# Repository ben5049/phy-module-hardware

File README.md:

# PHY Module Hardware

## 10BASE-T1S v1

[Errata](/docs/errata.md#1-10base-t1s-phy-module-v1)

## 1000BASE-T1 v1

[Errata](/docs/errata.md#2-1000base-t1-phy-module-v1)

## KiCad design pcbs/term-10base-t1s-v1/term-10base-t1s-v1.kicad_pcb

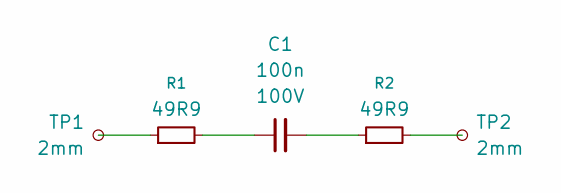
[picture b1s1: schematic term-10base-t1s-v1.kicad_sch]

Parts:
C1: 100n; C_0402_1005Metric; Voltage 100V
R1, R2: 49R9; R_0402_1005Metric
TP1, TP2: 2mm; TestPoint_Pad_D2.0mm

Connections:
unnamed: C1.1, R1.2
unnamed: C1.2, R2.1
unnamed: R1.1, TP1.1 (1_1)
unnamed: R2.2, TP2.1 (1_1)

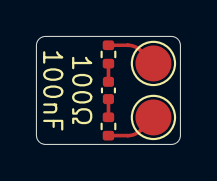
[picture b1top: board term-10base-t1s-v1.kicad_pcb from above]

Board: 2 copper layers, 8.0 x 6.0 mm, 5 parts (0 on the bottom side), 4 nets.

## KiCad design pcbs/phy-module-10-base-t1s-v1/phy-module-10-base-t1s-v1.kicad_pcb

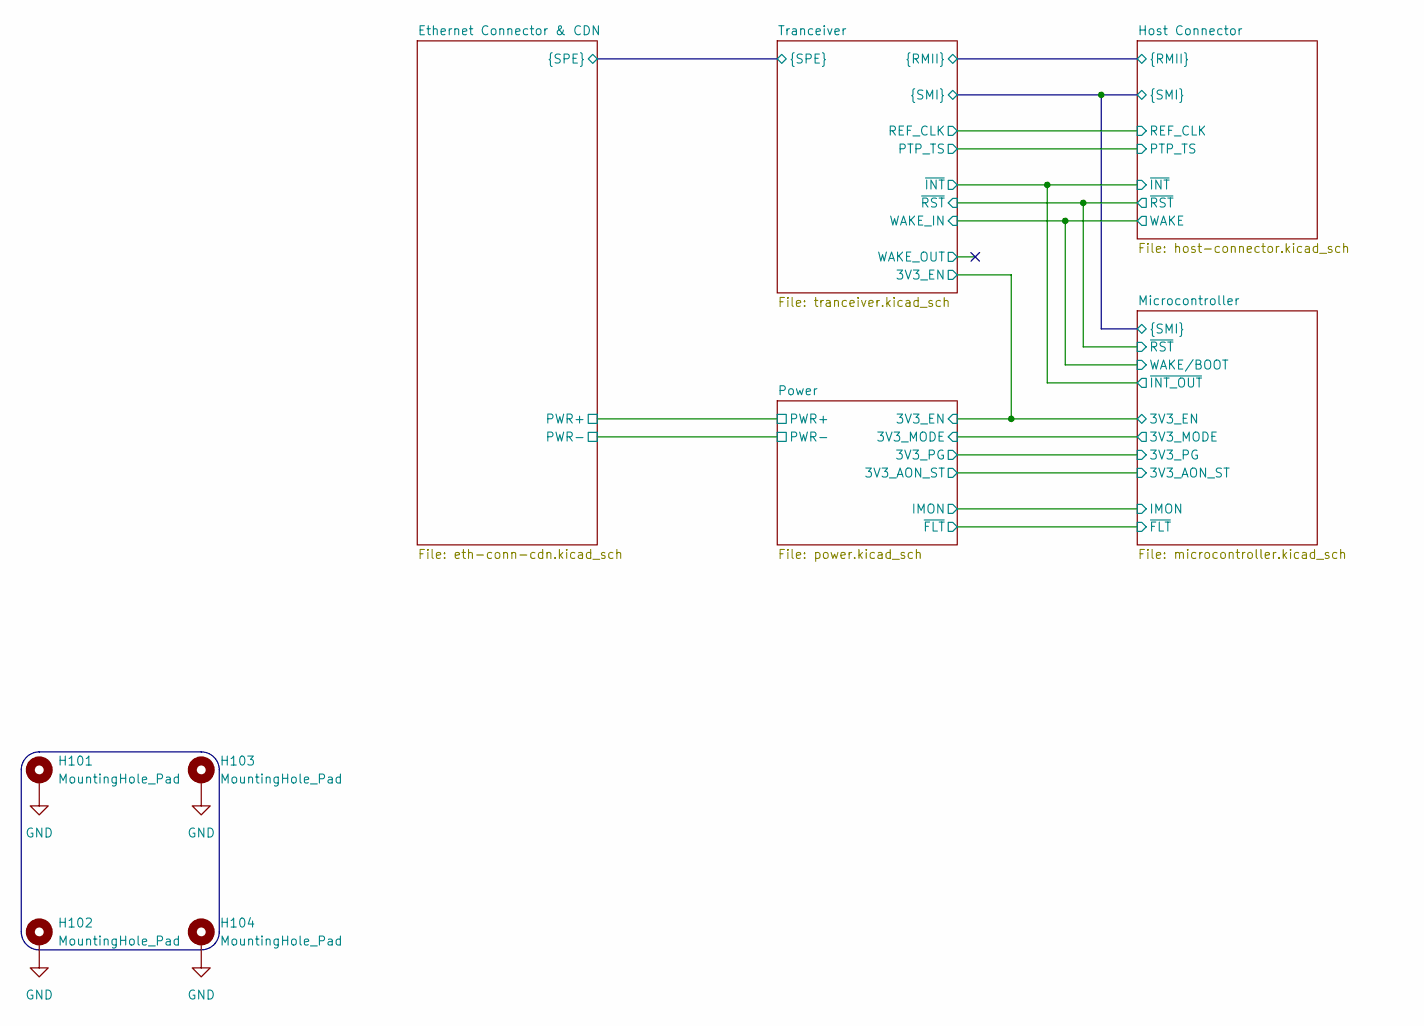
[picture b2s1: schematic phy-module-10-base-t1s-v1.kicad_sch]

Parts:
H101, H102, H103, H104: MountingHole_Pad; MountingHole_2.7mm_M2.5_Pad

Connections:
GND: H101.1 (1_1), H102.1 (1_1), H103.1 (1_1), H104.1 (1_1); also elsewhere on the board

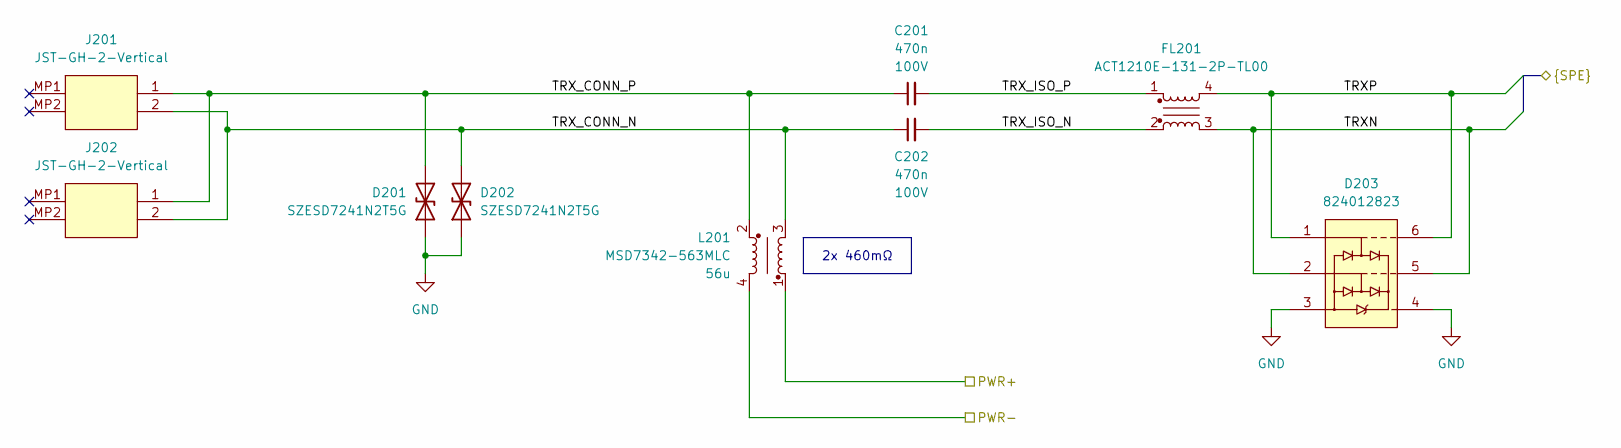
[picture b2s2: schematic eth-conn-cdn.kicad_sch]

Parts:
C201, C202: 470n; C_0805; Voltage 100V
D201, D202: SZESD7241N2T5G; SZESD7462N2T5G; Mouser Part Number 863-SZESD7241N2T5G
D203: 824012823; Mouser Part Number 710-824012823
FL201: ACT1210E-131-2P-TL00; ACT1210E; Mouser Part Number 810-ACT1210E1312PTL0
J201, J202: JST-GH-2-Vertical; JST_GH_BM02B-GHS-TBT_1x02-1MP_P1.25mm_Vertical
L201: MSD7342-563MLC; MSD7342

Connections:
/Ethernet Connector & CDN/PWR+: L201.1; also elsewhere on the board
/Ethernet Connector & CDN/PWR-: L201.4 (2); also elsewhere on the board
/Ethernet Connector & CDN/TRXN: D203.2, D203.5, FL201.3; also elsewhere on the board
/Ethernet Connector & CDN/TRXP: D203.1, D203.6, FL201.4; also elsewhere on the board
/Ethernet Connector & CDN/TRX_CONN_N: C202.1, D202.2 (A2), J201.2, J202.2, L201.3
/Ethernet Connector & CDN/TRX_CONN_P: C201.1, D201.2 (A2), J201.1, J202.1, L201.2 (4)
/Ethernet Connector & CDN/TRX_ISO_N: C202.2, FL201.2
/Ethernet Connector & CDN/TRX_ISO_P: C201.2, FL201.1
GND: D201.1 (A1), D202.1 (A1), D203.3, D203.4; also elsewhere on the board

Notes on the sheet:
2x 460mΩ

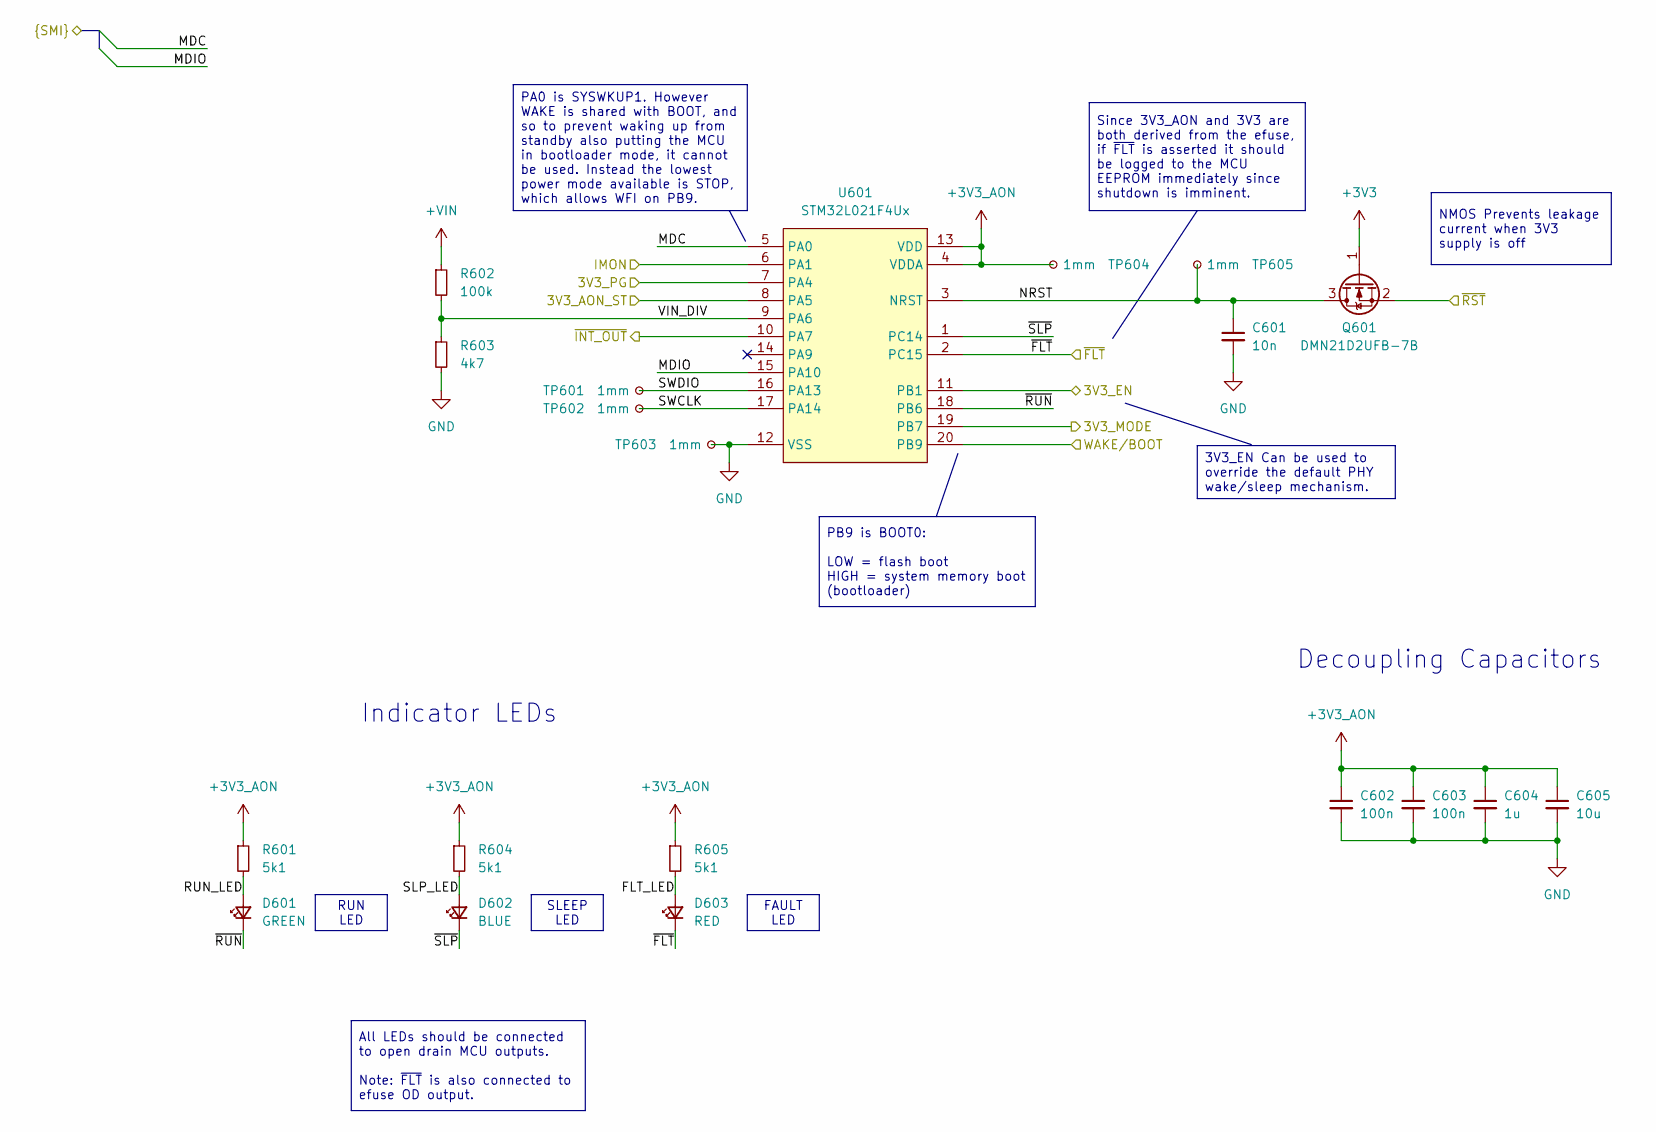
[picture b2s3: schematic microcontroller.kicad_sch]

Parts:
C601: 10n; C_0402
C602, C603: 100n; C_0402
C604: 1u; C_0402
C605: 10u; C_0402
D601: GREEN; LED_0402
D602: BLUE; LED_0402
D603: RED; LED_0402
Q601: DMN21D2UFB-7B; DMN21D2UFB7B; Mouser Part Number 621-DMN21D2UFB-7B
R601, R604, R605: 5k1; R_0402
R602: 100k; R_0402
R603: 4k7; R_0402
TP601, TP602, TP603, TP604, TP605: 1mm; TestPoint_Pad_D1.0mm
U601: STM32L021F4Ux; ST_UFQFPN-20_3x3mm_P0.5mm

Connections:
+3V3: Q601.1 (G); also elsewhere on the board
+3V3_AON: C602.1, C603.1, C604.1, C605.1, R601.1, R604.1, R605.1, TP604.1 (1_1), U601.4 (VDDA), U601.13 (VDD); also elsewhere on the board
+VIN: R602.1; also elsewhere on the board
/Host Connector/MDC: U601.5 (PA0); also elsewhere on the board
/Host Connector/MDIO: U601.15 (PA10); also elsewhere on the board
/Host Connector/WAKE: U601.20 (PB9); also elsewhere on the board
/Host Connector/~INT: U601.10 (PA7); also elsewhere on the board
/Host Connector/~RST: Q601.2 (S); also elsewhere on the board
/Microcontroller/3V3_AON_ST: U601.8 (PA5); also elsewhere on the board
/Microcontroller/3V3_EN: U601.11 (PB1); also elsewhere on the board
/Microcontroller/3V3_MODE: U601.19 (PB7); also elsewhere on the board
/Microcontroller/FLT_LED: D603.2 (A), R605.2
/Microcontroller/IMON: U601.6 (PA1); also elsewhere on the board
/Microcontroller/NRST: C601.1, Q601.3 (D), TP605.1 (1_1), U601.3 (NRST)
/Microcontroller/RUN_LED: D601.2 (A), R601.2
/Microcontroller/SLP_LED: D602.2 (A), R604.2
/Microcontroller/SWCLK: TP602.1 (1_1), U601.17 (PA14)
/Microcontroller/SWDIO: TP601.1 (1_1), U601.16 (PA13)
/Microcontroller/VIN_DIV: R602.2, R603.1, U601.9 (PA6)
/Microcontroller/~FLT: D603.1 (K), U601.2 (PC15); also elsewhere on the board
/Microcontroller/~RUN: D601.1 (K), U601.18 (PB6)
/Microcontroller/~SLP: D602.1 (K), U601.1 (PC14)
/Power/3V3_PG: U601.7 (PA4); also elsewhere on the board
GND: C601.2, C602.2, C603.2, C604.2, C605.2, R603.2, TP603.1 (1_1), U601.12 (VSS); also elsewhere on the board

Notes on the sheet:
Decoupling Capacitors
Indicator LEDs
RUN LED
PA0 is SYSWKUP1. However WAKE is shared with BOOT, and so to prevent waking up from standby also putting the MCU in bootloader mode, it cannot be used. Instead the lowest power mode available is STOP, which allows WFI on PB9.
PB9 is BOOT0: LOW = flash boot HIGH = system memory boot (bootloader)
FAULT LED
Since 3V3_AON and 3V3 are both derived from the efuse, if ~{FLT} is asserted it should be logged to the MCU EEPROM immediately since shutdown is imminent.
SLEEP LED
All LEDs should be connected to open drain MCU outputs. Note: ~{FLT} is also connected to efuse OD output.
3V3_EN Can be used to override the default PHY wake/sleep mechanism.
NMOS Prevents leakage current when 3V3 supply is off

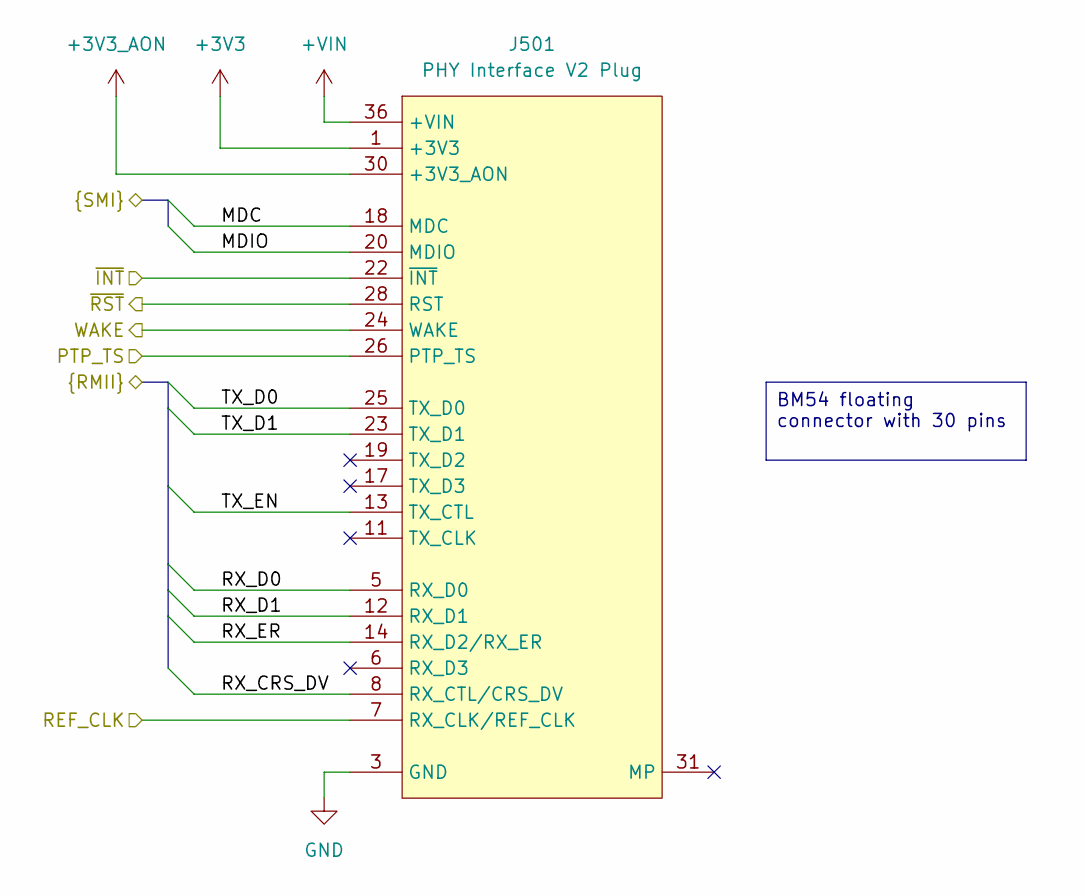
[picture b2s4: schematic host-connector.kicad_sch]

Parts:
J501: PHY Interface V2 Plug; BM54F3030DP04V51-PWR

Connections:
+3V3: J501.1 (+3V3), J501.2 (+3V3), J501.29 (+3V3); also elsewhere on the board
+3V3_AON: J501.30 (+3V3_AON); also elsewhere on the board
+VIN: J501.36 (+VIN); also elsewhere on the board
/Host Connector/MDC: J501.18 (MDC); also elsewhere on the board
/Host Connector/MDIO: J501.20 (MDIO); also elsewhere on the board
/Host Connector/PTP_TS: J501.26 (PTP_TS); also elsewhere on the board
/Host Connector/REF_CLK: J501.7 (RX_CLK/REF_CLK); also elsewhere on the board
/Host Connector/RX_CRS_DV: J501.8 (RX_CTL/CRS_DV); also elsewhere on the board
/Host Connector/RX_D0: J501.5 (RX_D0); also elsewhere on the board
/Host Connector/RX_D1: J501.12 (RX_D1); also elsewhere on the board
/Host Connector/RX_ER: J501.14 (RX_D2/RX_ER); also elsewhere on the board
/Host Connector/TX_D0: J501.25 (TX_D0); also elsewhere on the board
/Host Connector/TX_D1: J501.23 (TX_D1); also elsewhere on the board
/Host Connector/TX_EN: J501.13 (TX_CTL); also elsewhere on the board
/Host Connector/WAKE: J501.24 (WAKE); also elsewhere on the board
/Host Connector/~INT: J501.22 (~INT); also elsewhere on the board
/Host Connector/~RST: J501.28 (RST); also elsewhere on the board
GND: J501.3 (GND), J501.4 (GND), J501.9 (GND), J501.10 (GND), J501.15 (GND), J501.16 (GND), J501.21 (GND), J501.27 (GND), J501.35 (GND); also elsewhere on the board

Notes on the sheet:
BM54 floating connector with 30 pins

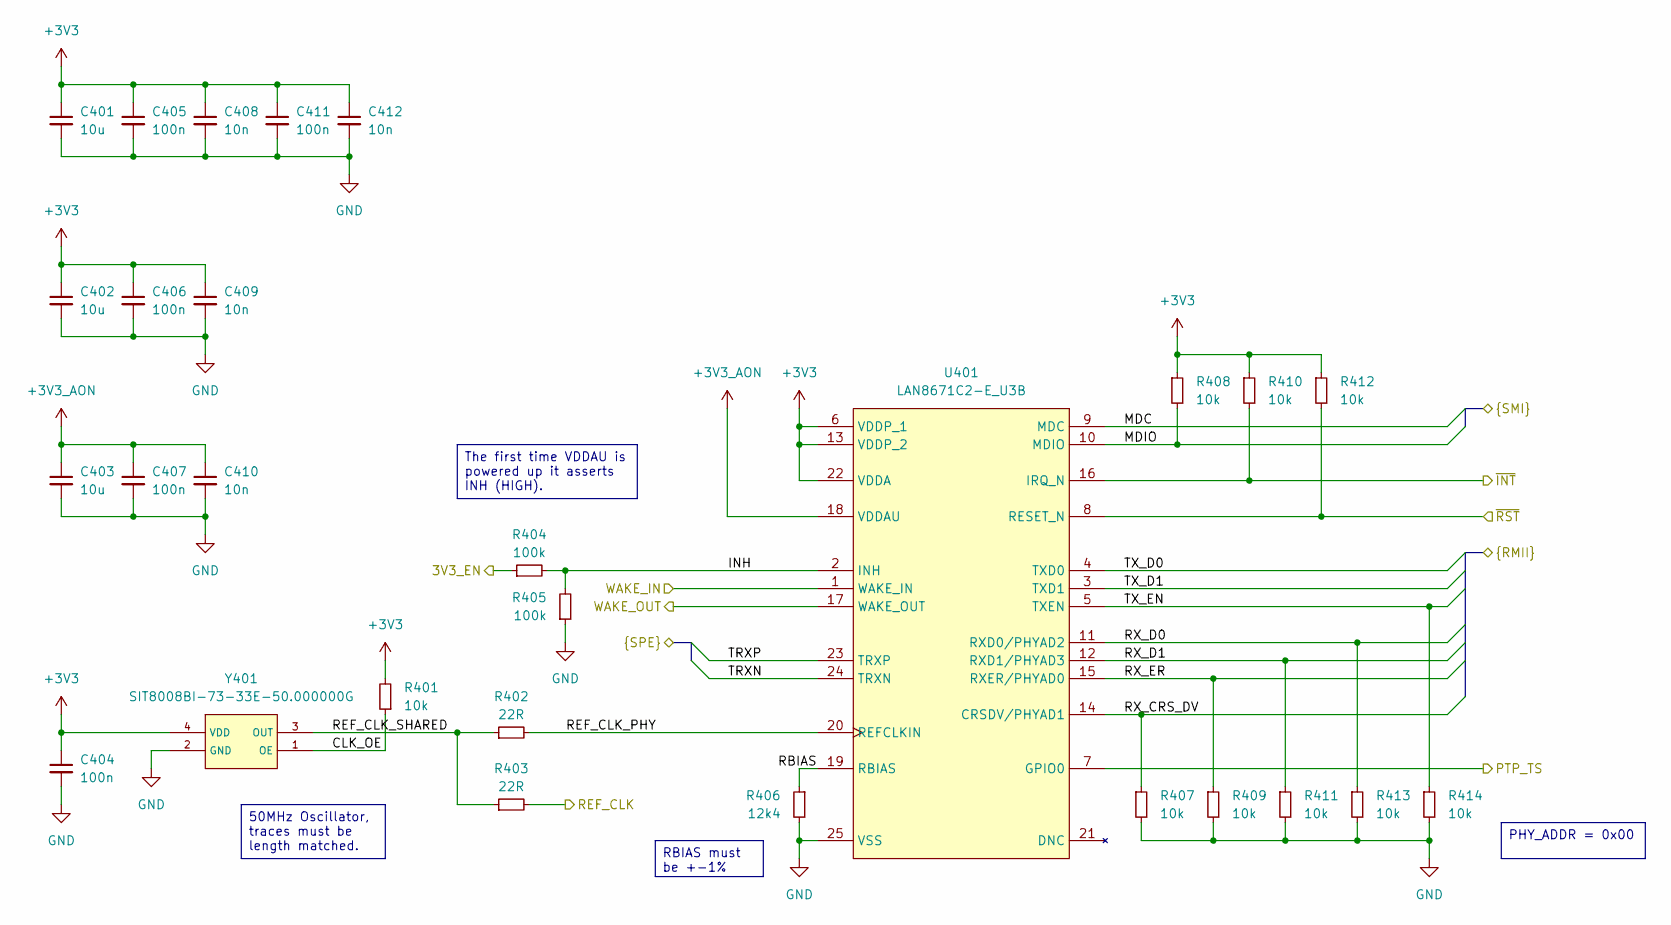
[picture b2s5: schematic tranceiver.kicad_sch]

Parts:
C401, C402, C403: 10u; C_0402
C404, C405, C406, C407, C411: 100n; C_0402
C408, C409, C410, C412: 10n; C_0402
R401, R407, R408, R409, R410, R411, R412, R413, R414: 10k; R_0402
R402, R403: 22R; R_0402
R404, R405: 100k; R_0402
R406: 12k4; R_0402
U401: LAN8671C2-E_U3B; QFN50P400X400X100-25N-D; Mouser Part Number 579-LAN8671C2-E/U3B
Y401: SIT8008BI-73-33E-50.000000G; SiTime-SiT8008-7-0-0-MFG; mouser part number 788-8008BI7333E500G; digikey description MEMS OSC XO 50.0000MHZ H/LV-CMOS

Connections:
+3V3: C401.1, C402.1, C404.1, C405.1, C406.1, C408.1, C409.1, C411.1, C412.1, R401.2, R408.1, R410.1, R412.1, U401.6 (VDDP_1), U401.13 (VDDP_2), U401.22 (VDDA), Y401.4 (VDD); also elsewhere on the board
+3V3_AON: C403.1, C407.1, C410.1, U401.18 (VDDAU); also elsewhere on the board
/Ethernet Connector & CDN/TRXN: U401.24 (TRXN); also elsewhere on the board
/Ethernet Connector & CDN/TRXP: U401.23 (TRXP); also elsewhere on the board
/Host Connector/MDC: U401.9 (MDC); also elsewhere on the board
/Host Connector/MDIO: R408.2, U401.10 (MDIO); also elsewhere on the board
/Host Connector/PTP_TS: U401.7 (GPIO0); also elsewhere on the board
/Host Connector/REF_CLK: R403.2; also elsewhere on the board
/Host Connector/RX_CRS_DV: R407.1, U401.14 (CRSDV/PHYAD1); also elsewhere on the board
/Host Connector/RX_D0: R413.1, U401.11 (RXD0/PHYAD2); also elsewhere on the board
/Host Connector/RX_D1: R411.1, U401.12 (RXD1/PHYAD3); also elsewhere on the board
/Host Connector/RX_ER: R409.1, U401.15 (RXER/PHYAD0); also elsewhere on the board
/Host Connector/TX_D0: U401.4 (TXD0); also elsewhere on the board
/Host Connector/TX_D1: U401.3 (TXD1); also elsewhere on the board
/Host Connector/TX_EN: R414.1, U401.5 (TXEN); also elsewhere on the board
/Host Connector/WAKE: U401.1 (WAKE_IN); also elsewhere on the board
/Host Connector/~INT: R410.2, U401.16 (IRQ_N); also elsewhere on the board
/Host Connector/~RST: R412.2, U401.8 (RESET_N); also elsewhere on the board
/Microcontroller/3V3_EN: R404.1; also elsewhere on the board
/Tranceiver/CLK_OE: R401.1, Y401.1 (OE)
/Tranceiver/INH: R404.2, R405.2, U401.2 (INH)
/Tranceiver/RBIAS: R406.1, U401.19 (RBIAS)
/Tranceiver/REF_CLK_PHY: R402.2, U401.20 (REFCLKIN)
/Tranceiver/REF_CLK_SHARED: R402.1, R403.1, Y401.3 (OUT)
/Tranceiver/WAKE_OUT: U401.17 (WAKE_OUT)
GND: C401.2, C402.2, C403.2, C404.2, C405.2, C406.2, C407.2, C408.2, C409.2, C410.2, C411.2, C412.2, R405.1, R406.2, R407.2, R409.2, R411.2, R413.2, R414.2, U401.25 (VSS), Y401.2 (GND); also elsewhere on the board

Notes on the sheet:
50MHz Oscillator, traces must be length matched.
PHY_ADDR = 0x00
RBIAS must be +-1%
The first time VDDAU is powered up it asserts INH (HIGH).

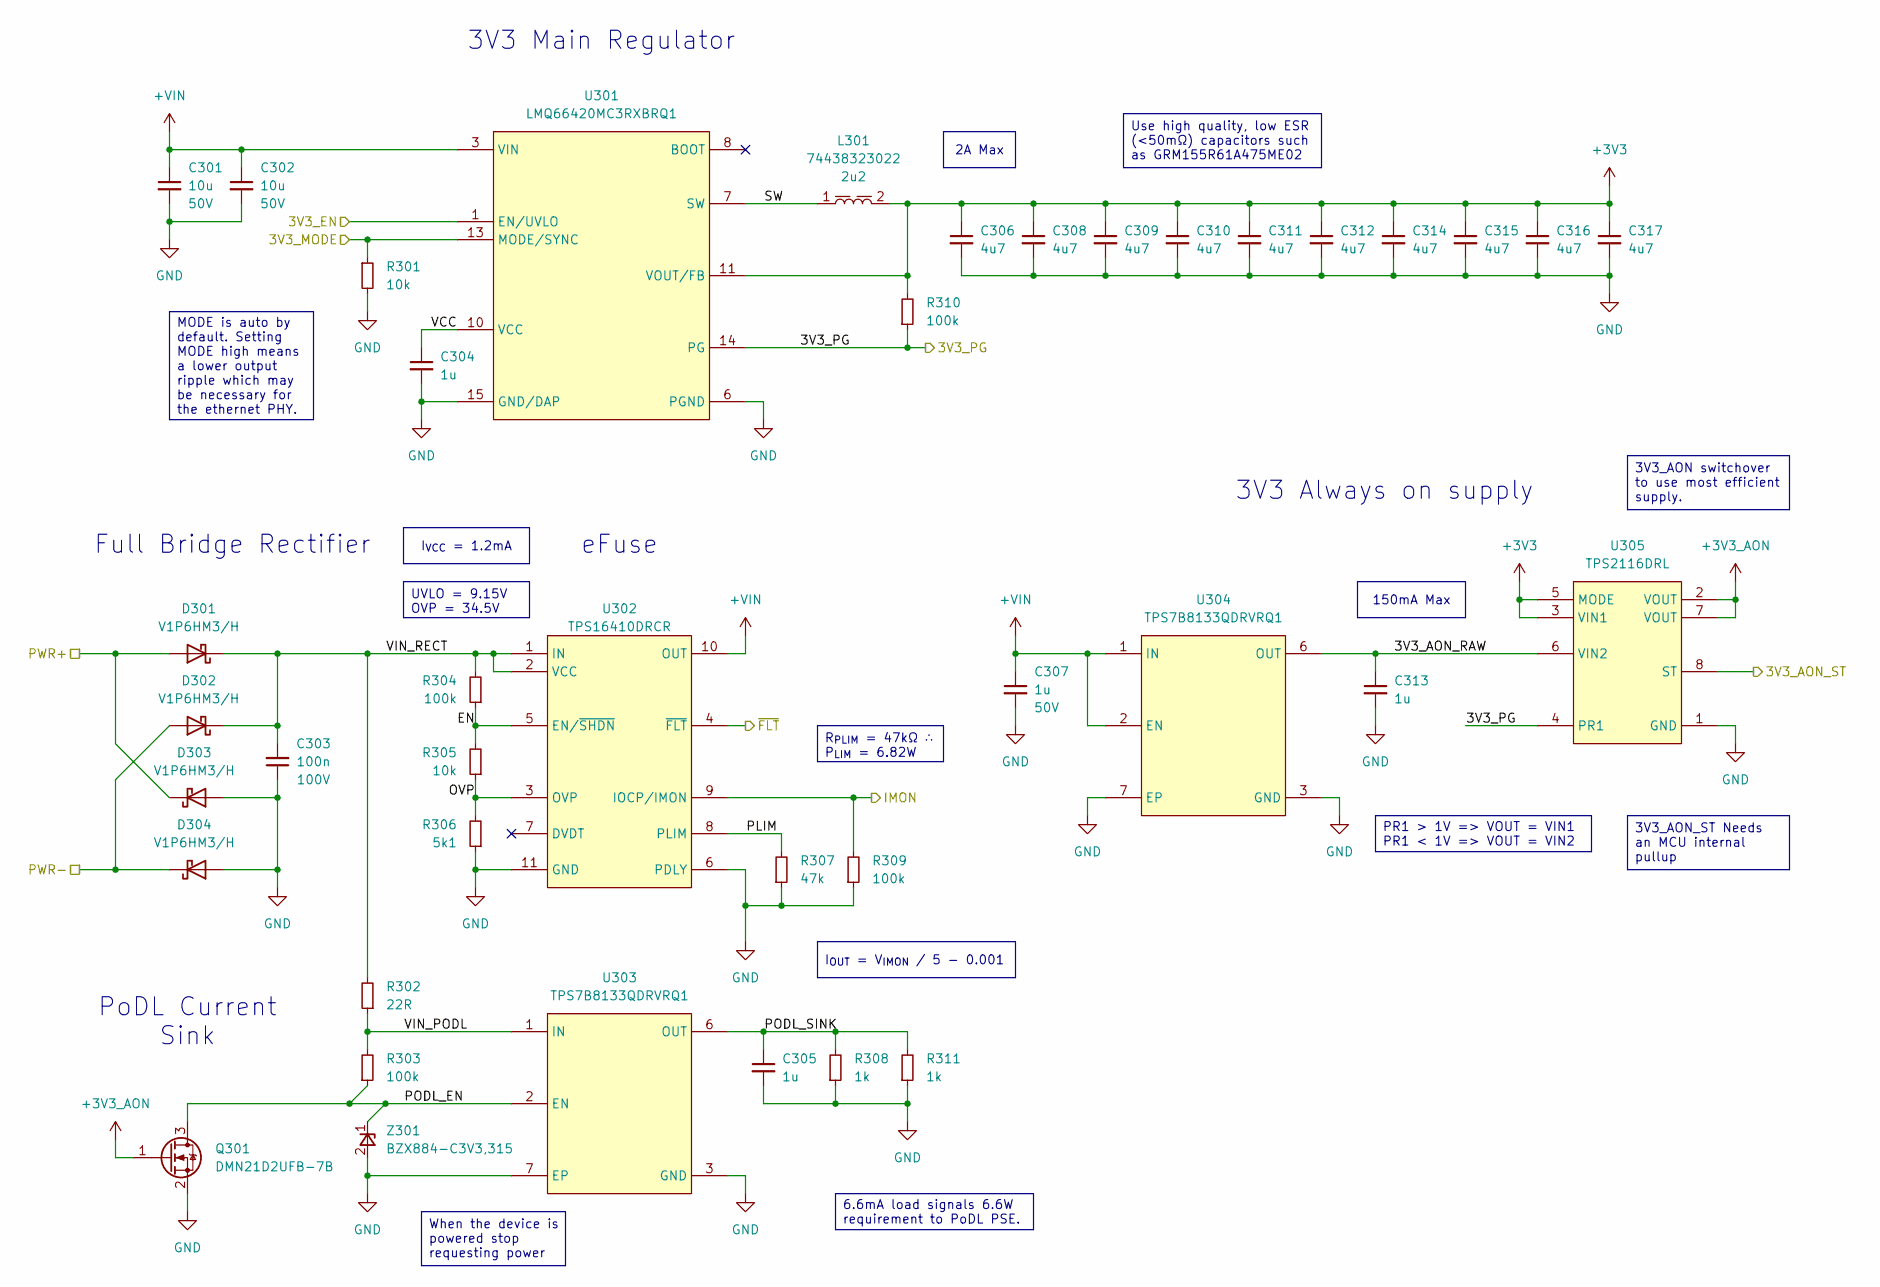
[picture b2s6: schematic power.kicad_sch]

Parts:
C301, C302: 10u; C_0805; Voltage 50V
C303: 100n; C_0402; Voltage 100V
C304, C305, C313: 1u; C_0402
C306, C308, C309, C310, C311, C312, C314, C315, C316, C317: 4u7; C_0402
C307: 1u; C_0402; Voltage 50V
D301, D302, D303, D304: V1P6HM3/H; V1P6HM3_H
L301: 74438323022; L_Wurth_WE-MAPI-2510; Part Number 74438323022
Q301: DMN21D2UFB-7B; DMN21D2UFB7B; Mouser Part Number 621-DMN21D2UFB-7B
R301, R305: 10k; R_0402
R302: 22R; R_0402
R303, R304, R309, R310: 100k; R_0402
R306: 5k1; R_0402
R307: 47k; R_0402
R308, R311: 1k; R_0402
U301: LMQ66420MC3RXBRQ1; LMQ664x0
U302: TPS16410DRCR; Mouser Part Number 595-TPS16410DRCR
U303, U304: TPS7B8133QDRVRQ1; SON65P200X200X80-7N; Mouser Part Number 595-TPS7B8133QDRVRQ1
U305: TPS2116DRL; SOTFL50P160X60-8N
Z301: BZX884-C3V3,315; BZX884; Mouser Part Number 771-BZX884-C3V9315

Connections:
+3V3: C306.1, C308.1, C309.1, C310.1, C311.1, C312.1, C314.1, C315.1, C316.1, C317.1, L301.2, R310.2, U301.11 (VOUT/FB), U305.3 (VIN1), U305.5 (MODE); also elsewhere on the board
+3V3_AON: Q301.1 (G), U305.2 (VOUT), U305.7 (VOUT); also elsewhere on the board
+VIN: C301.1, C302.1, C307.1, U301.3 (VIN), U302.10 (OUT), U304.1 (IN), U304.2 (EN); also elsewhere on the board
/Ethernet Connector & CDN/PWR+: D301.2 (A), D303.1 (K); also elsewhere on the board
/Ethernet Connector & CDN/PWR-: D302.2 (A), D304.1 (K); also elsewhere on the board
/Microcontroller/3V3_AON_ST: U305.8 (ST); also elsewhere on the board
/Microcontroller/3V3_EN: U301.1 (EN/UVLO); also elsewhere on the board
/Microcontroller/3V3_MODE: R301.1, U301.13 (MODE/SYNC); also elsewhere on the board
/Microcontroller/IMON: R309.2, U302.9 (IOCP/IMON); also elsewhere on the board
/Microcontroller/~FLT: U302.4 (~FLT); also elsewhere on the board
/Power/3V3_AON_RAW: C313.1, U304.6 (OUT), U305.6 (VIN2)
/Power/3V3_PG: R310.1, U301.14 (PG), U305.4 (PR1); also elsewhere on the board
/Power/EN: R304.1, R305.2, U302.5 (EN/~SHDN)
/Power/OVP: R305.1, R306.2, U302.3 (OVP)
/Power/PLIM: R307.2, U302.8 (PLIM)
/Power/PODL_EN: Q301.3 (D), R303.1, U303.2 (EN), Z301.1 (K)
/Power/PODL_SINK: C305.1, R308.2, R311.2, U303.6 (OUT)
/Power/SW: L301.1, U301.7 (SW)
/Power/VCC: C304.1, U301.10 (VCC)
/Power/VIN_PODL: R302.1, R303.2, U303.1 (IN)
/Power/VIN_RECT: C303.2, D301.1 (K), D302.1 (K), R302.2, R304.2, U302.1 (IN), U302.2 (VCC)
GND: C301.2, C302.2, C303.1, C304.2, C305.2, C306.2, C307.2, C308.2, C309.2, C310.2, C311.2, C312.2, C313.2, C314.2, C315.2, C316.2, C317.2, D303.2 (A), D304.2 (A), Q301.2 (S), R301.2, R306.1, R307.1, R308.1, R309.1, R311.1, U301.6 (PGND), U301.15 (GND/DAP), U302.6 (PDLY), U302.11 (GND), U302.12 (GND), U302.13 (GND), U302.14 (GND), U302.15 (GND), U303.3 (GND), U303.4 (GND), U303.7 (EP), U304.3 (GND), U304.4 (GND), U304.7 (EP), U305.1 (GND), Z301.2 (A); also elsewhere on the board

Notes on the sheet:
Full Bridge Rectifier
PoDL Current Sink
3V3 Main Regulator
3V3 Always on supply
eFuse
R_{PLIM} = 47kΩ ∴ P_{LIM} = 6.82W
UVLO = 9.15V OVP = 34.5V
MODE is auto by default. Setting MODE high means a lower output ripple which may be necessary for the ethernet PHY.
When the device is powered stop requesting power
PR1 > 1V => VOUT = VIN1 PR1 < 1V => VOUT = VIN2
3V3_AON switchover to use most efficient supply.
2A Max
Use high quality, low ESR (<50mΩ) capacitors such as GRM155R61A475ME02
150mA Max
3V3_AON_ST Needs an MCU internal pullup
6.6mA load signals 6.6W requirement to PoDL PSE.
I_{VCC} = 1.2mA
I_{OUT} = V_{IMON} / 5 - 0.001

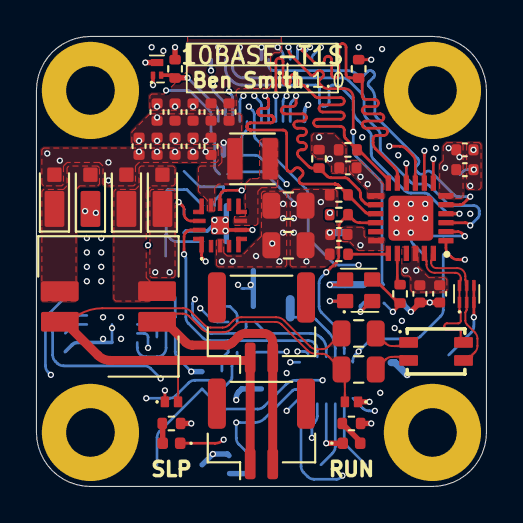
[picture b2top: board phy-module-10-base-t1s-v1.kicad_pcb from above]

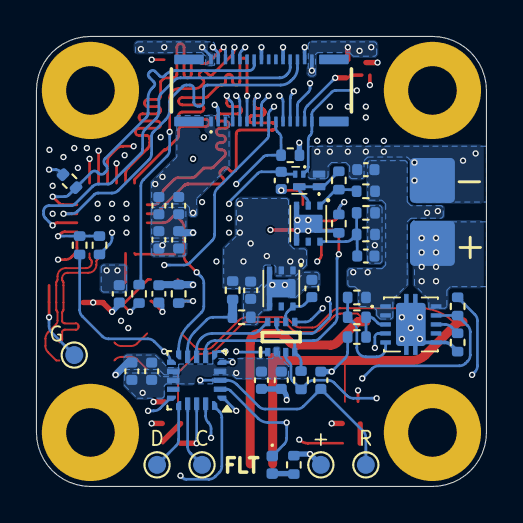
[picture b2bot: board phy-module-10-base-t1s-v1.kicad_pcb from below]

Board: 6 copper layers, 25.0 x 25.0 mm, 102 parts (50 on the bottom side), 56 nets.

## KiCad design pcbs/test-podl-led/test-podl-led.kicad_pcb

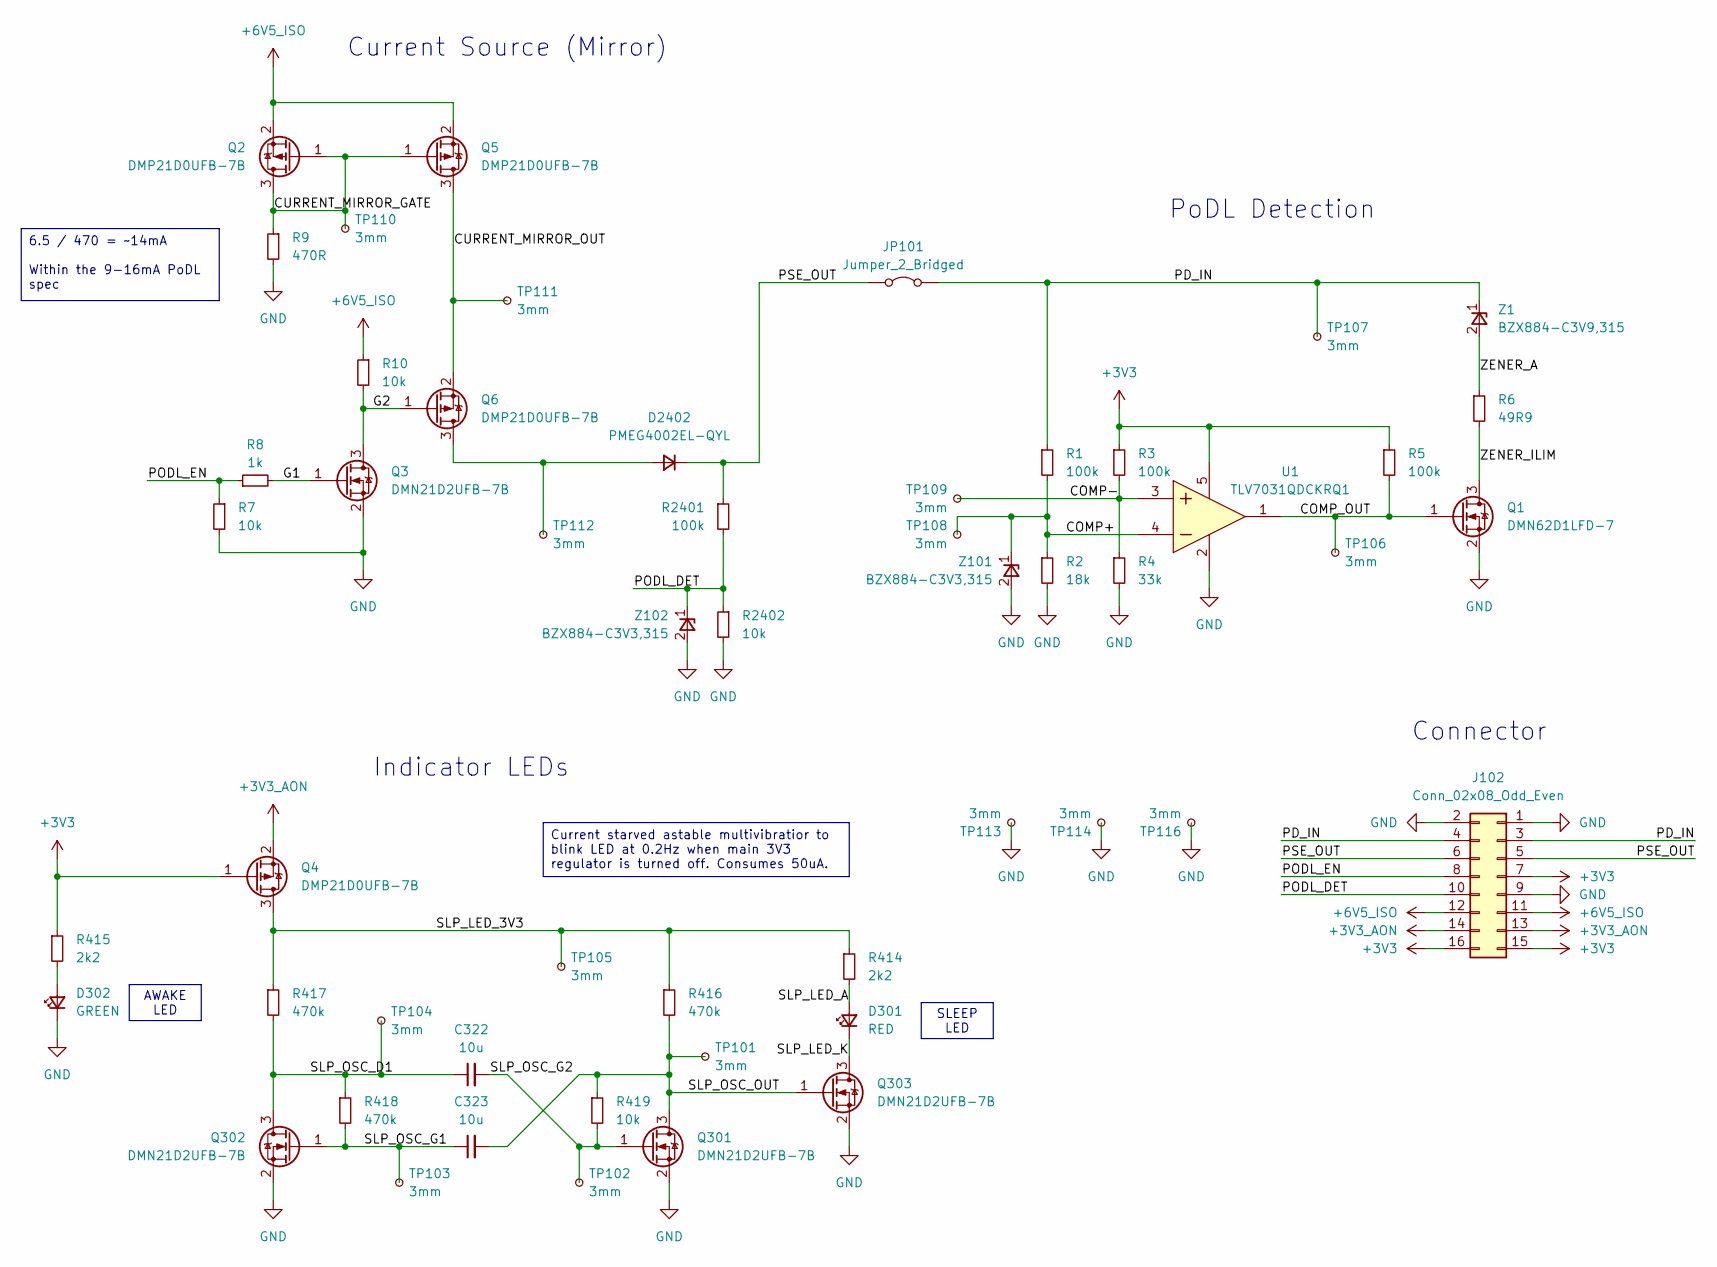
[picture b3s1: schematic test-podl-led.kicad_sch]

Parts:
C322, C323: 10u; C_0402_1005Metric
D301: RED; LED_0402_1005Metric
D302: GREEN; LED_0402_1005Metric
D2402: PMEG4002EL-QYL
J102: Conn_02x08_Odd_Even; PinHeader_2x08_P2.54mm_Vertical
JP101: Jumper_2_Bridged; PinHeader_1x02_P2.54mm_Vertical
Q1: DMN62D1LFD-7; DMN62D1LFD; Mouser Part Number 621-DMN62D1LFD-7
Q2, Q4, Q5, Q6: DMP21D0UFB-7B; DMP21D0UFB7B; Mouser Part Number 621-DMP21D0UFB-7B
Q3, Q301, Q302, Q303: DMN21D2UFB-7B; DMN21D2UFB7B; Mouser Part Number 621-DMN21D2UFB-7B
R1, R3, R5, R2401: 100k; R_0402_1005Metric
R2: 18k; R_0402_1005Metric
R4: 33k; R_0402_1005Metric
R6: 49R9; R_0402_1005Metric
R7, R10, R419, R2402: 10k; R_0402_1005Metric
R8: 1k; R_0402_1005Metric
R9: 470R; R_0402_1005Metric
R414, R415: 2k2; R_0402_1005Metric
R416, R417, R418: 470k; R_0402_1005Metric
TP101, TP102, TP103, TP104, TP105, TP106, TP107, TP108, TP109, TP110, TP111, TP112, TP113, TP114, TP116: 3mm; TestPoint_Pad_D3.0mm
U1: TLV7031QDCKRQ1; SOT65P210X110-5N; Mouser Part Number 595-TLV7031QDCKRQ1
Z1: BZX884-C3V9,315; BZX884; Mouser Part Number 771-BZX884-C3V9315
Z101, Z102: BZX884-C3V3,315; BZX884; Mouser Part Number 771-BZX884-C3V9315

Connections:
+3V3: J102.7, J102.15, J102.16, Q4.1 (G), R3.1, R5.1, R415.1, U1.5 (VCC)
+3V3_AON: J102.13, J102.14, Q4.2 (S)
+6V5_ISO: J102.11, J102.12, Q2.2 (S), Q5.2 (S), R10.1
/COMP+: R1.2, R2.1, TP108.1, U1.4 (IN-), Z101.1 (K)
/COMP-: R3.2, R4.1, TP109.1, U1.3 (IN+)
/COMP_OUT: Q1.1 (G), R5.2, TP106.1, U1.1 (OUT)
/CURRENT_MIRROR_GATE: Q2.1 (G), Q2.3 (D), Q5.1 (G), R9.1, TP110.1
/CURRENT_MIRROR_OUT: Q5.3 (D), Q6.2 (S), TP111.1
/G1: Q3.1 (G), R8.2
/G2: Q3.3 (D), Q6.1 (G), R10.2
/PD_IN: J102.3, J102.4, JP101.2 (B), R1.1, TP107.1, Z1.1 (K)
/PODL_DET: J102.10, R2401.2, R2402.1, Z102.1 (K)
/PODL_EN: J102.8, R7.1, R8.1
/PSE_OUT: D2402.1 (K), J102.5, J102.6, JP101.1 (A), R2401.1
/SLP_LED_3V3: Q4.3 (D), R414.1, R416.1, R417.1, TP105.1
/SLP_LED_A: D301.2 (A), R414.2
/SLP_LED_K: D301.1 (K), Q303.3 (D)
/SLP_OSC_D1: C322.1, Q302.3 (D), R417.2, R418.1, TP104.1
/SLP_OSC_G1: C323.1, Q302.1 (G), R418.2, TP103.1
/SLP_OSC_G2: C322.2, Q301.1 (G), R419.2, TP102.1
/SLP_OSC_OUT: C323.2, Q301.3 (D), Q303.1 (G), R416.2, R419.1, TP101.1
/ZENER_A: R6.1, Z1.2 (A)
/ZENER_ILIM: Q1.3 (D), Q1.4 (D), R6.2
GND: D302.1 (K), J102.1, J102.2, J102.9, Q1.2 (S), Q3.2 (S), Q301.2 (S), Q302.2 (S), Q303.2 (S), R2.2, R4.2, R7.2, R9.2, R2402.2, TP113.1, TP114.1, TP116.1, U1.2 (VEE), Z101.2 (A), Z102.2 (A)
unnamed: D302.2 (A), R415.2
unnamed: D2402.2 (A), Q6.3 (D), TP112.1

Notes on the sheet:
Connector
PoDL Detection
Indicator LEDs
Current Source (Mirror)
SLEEP LED
6.5 / 470 = ~14mA Within the 9-16mA PoDL spec
Current starved astable multivibratior to blink LED at 0.2Hz when main 3V3 regulator is turned off. Consumes 50uA.
AWAKE LED

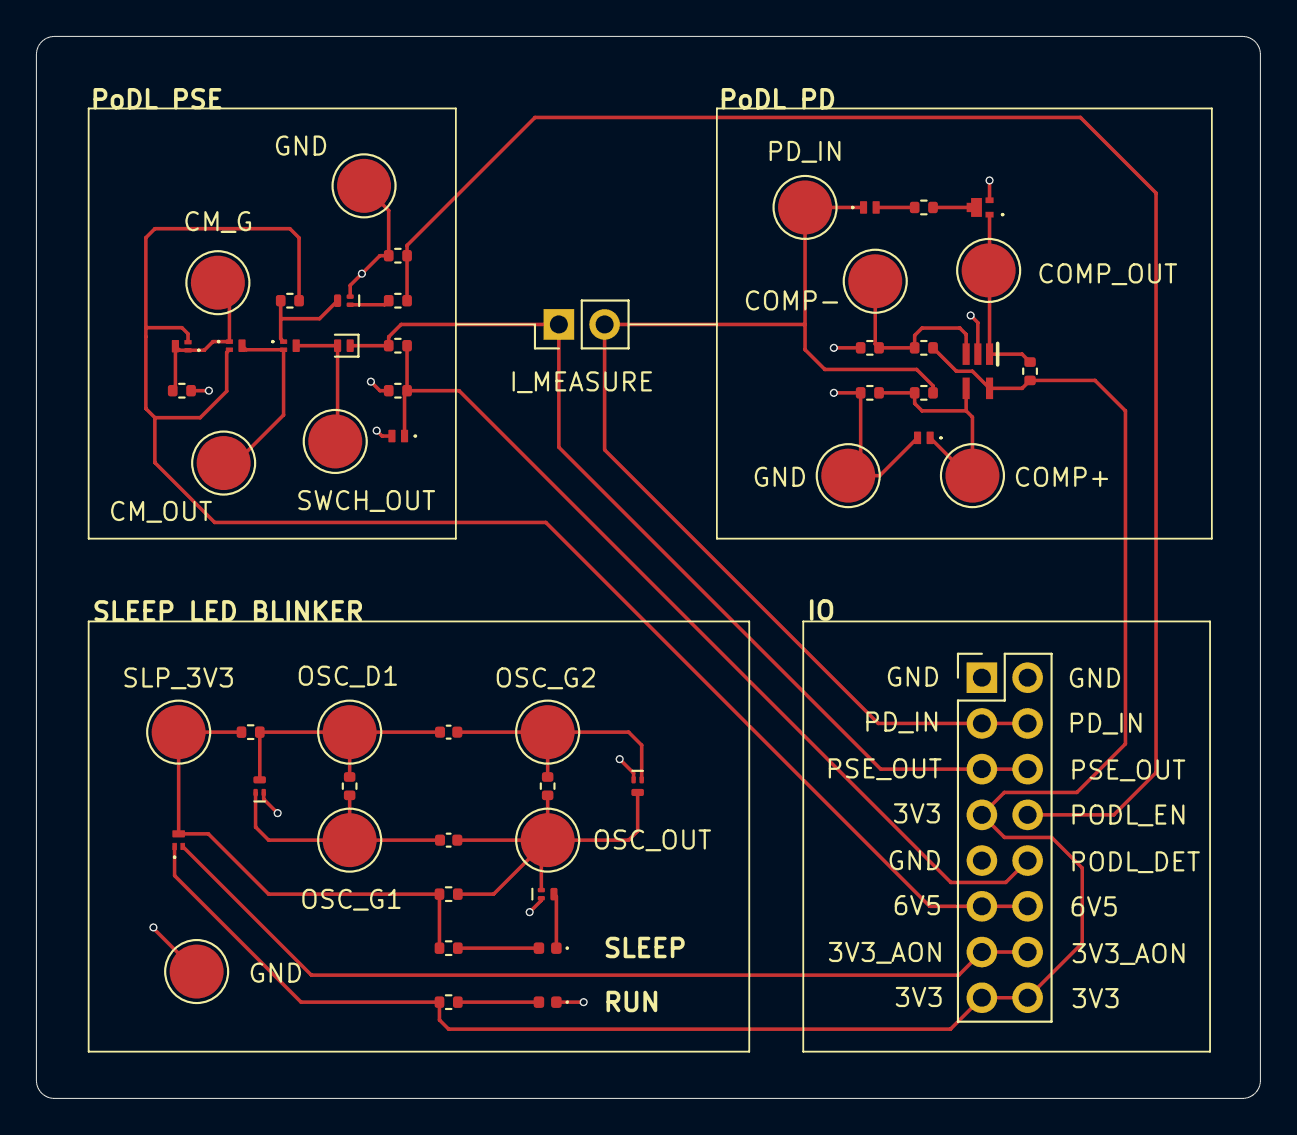
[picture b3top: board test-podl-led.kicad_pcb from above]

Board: 2 copper layers, 68.0 x 59.0 mm, 53 parts (0 on the bottom side), 26 nets.
